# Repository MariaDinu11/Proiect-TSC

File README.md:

# Proiect-TSC

  OpenBook E-Reader
OpenBook este un e-book reader open source si accesibil, proiectat pentru a oferi o experiență bună de citire la un preț competitiv.

## Bill of Materials (BOM)

| Nr. | Componenta | Descriere | Cantitate | Link achizitie | Datasheet |
|-----|------------|-----------|-----------|----------------|-----------|
| 1 | ESP32-C6-WROOM-1-N8 | Modul WiFi/Bluetooth/Zigbee | 1 | [Model](https://www.snapeda.com/parts/ESP32-C6-WROOM-1-N8/Espressif+Systems/view-part/?ref=eda) | [Datasheet](https://www.espressif.com/sites/default/files/documentation/esp32-c6_datasheet_en.pdf) |
| 2 | W25Q512JVEIQ | Memorie Flash NOR 64MB | 1 | [Model](https://www.snapeda.com/parts/W25Q512JVEIQ/Winbond+Electronics/view-part/?ref=eda) | [Datasheet](https://www.winbond.com/resource-files/W25Q512JV%20RevI%2005132020%20Plus.pdf) |
| 3 | DS3231SN# | Modul RTC de inalta precizie | 1 | [Model](https://www.snapeda.com/parts/DS3231SN%23/Analog+Devices/view-part/?ref=eda) | [Datasheet](https://datasheets.maximintegrated.com/en/ds/DS3231.pdf) |
| 4 | MAX17048G+T10 | Controlor pentru monitorizarea bateriei | 1 | [Model](https://www.snapeda.com/parts/MAX17048G+T10/Analog+Devices/view-part/?ref=eda) | [Datasheet](https://datasheets.maximintegrated.com/en/ds/MAX17048-MAX17049.pdf) |
| 5 | BME688 | Senzor integrat de mediu | 1 | [Model](https://www.snapeda.com/parts/BME680/Bosch/view-part/?welcome=home) | [Datasheet](https://www.bosch-sensortec.com/media/boschsensortec/downloads/datasheets/bst-bme688-ds000.pdf) |
| 6 | MCP73831 | Controler de incarcare baterie Li-Po | 1 | [Model](https://www.mouser.co.uk/ProductDetail/Microchip-Technology/MCP73831T-5ACI-OT?qs=hH%252BOa0VZEiAcgAcEkuamXg%3D%3D) | [Datasheet](https://ww1.microchip.com/downloads/en/DeviceDoc/20001984g.pdf) |
| 7 | BD5229G-TR | Detector de tensiune cu timp de intarziere | 1 | [Model](https://componentsearchengine.com/part-view/BD5229G-TR/ROHM%20Semiconductor) | [Datasheet](https://fscdn.rohm.com/en/products/databook/datasheet/ic/power/voltage_detector/bd52xxg-e.pdf) |
| 8 | PFMF.050.1 | Conector USB Type-C | 1 | [Model](https://www.mouser.com/ProductDetail/Amphenol-FCI/PFMF0501?qs=sGAEpiMZZMulM8LYMF8bxyg6IYwX%252B5CgQVcIoLYkYiM%3D) | [Datasheet](https://cdn.amphenol-cs.com/media/wysiwyg/files/drawing/pfmf.pdf) |
| 9 | USBLC6-2SC6Y | Protectie ESD pentru linii USB | 1 | [Model](https://www.snapeda.com/parts/USBLC6-2SC6Y/STMicroelectronics/view-part/?ref=eda) | [Datasheet](https://www.st.com/resource/en/datasheet/usblc6-2.pdf) |
| 10 | 112A-TAAR-R03 | Slot pentru card microSD | 1 | [Model](https://www.mouser.com/ProductDetail/Attend/112A-TAAR-R03?qs=sGAEpiMZZMsg%2By7HCF96QHhTCuZhYGBTHJ9NEpPMzZc%3D) | [Datasheet](https://www.attend.com.tw/sites/default/files/2022-05/112A-TAAR-R03.pdf) |
| 11 | FH34SRJ-24S-0.5SH | Conector pentru ecran e-paper | 1 | [Model](https://www.hirose.com/product/p/CL0684-0832-7-99) | [Datasheet](https://www.hirose.com/product/document?clcode=CL0684-0832-7-99&productname=FH34SRJ-24S-0.5SH(99)&series=FH34&documenttype=Catalog&lang=en&documentid=D49681_en) |
| 12 | DMG2305UX-7 | Tranzistor MOSFET-P 20V/4.2A | 1 | [Model](https://www.diodes.com/part/view/DMG2305UX) | [Datasheet](https://www.diodes.com/assets/Datasheets/DMG2305UX.pdf) |
| 13 | SI1308EDL-T1-GE3 | Tranzistor MOSFET-N 30V/1.5A | 1 | [Model](https://www.snapeda.com/parts/SI1308EDL-T1-GE3/Vishay+Siliconix/view-part/?ref=snap) | [Datasheet](https://www.vishay.com/docs/68732/si1308edl.pdf) |
| 14 | SD0805S020S1R0 | Inductor 1.0µH | 1 | [Model](https://eu.mouser.com/ProductDetail/KYOCERA-AVX/SD0805S020S1R0?qs=jCA%252BPfw4LHbpkAoSnwrdjw%3D%3D) | [Datasheet](http://datasheets.avx.com/schottky.pdf) |
| 15 | MBR0530 | Dioda Schottky 30V/500mA | 3 | [Model](https://www.snapeda.com/parts/MBR0530/Onsemi/view-part/?ref=eda) | [Datasheet](https://www.onsemi.com/pdf/datasheet/mbr0520lt1-d.pdf) |
| 16 | PGB1010603MR | Dioda TVS pentru protectie ESD | 5 | [Model](https://www.snapeda.com/parts/PGB1010603MR/Littelfuse/view-part/?ref=eda) | [Datasheet](https://www.littelfuse.com/media?resourcetype=datasheets&itemid=3d1e98b7-4d37-463c-9380-c56c83b11c3c&filename=littelfuse-pulseguard-pgb1) |
| 17 | CPH3225A | Cristal RTC 32.768kHz | 1 | [Model](https://www.snapeda.com/parts/CPH3225A/Seiko+Instruments/view-part/?ref=eda) | [Datasheet](https://www.sii.co.jp/en/quartz/files/2021/03/CPH3225A_E.pdf) |
| 18 | XC6220A331MR-G | Regulator LDO de tensiune 3.3V | 1 | [Model](https://www.torexsemi.com/products/voltage-regulators/ldo-regulators/xc6220/) | [Datasheet](https://www.torexsemi.com/file/xc6220/XC6220.pdf) |
| 19 | Buton tactil | Butoane pentru Reset, Boot, Change | 3 | [Model](https://industry.panasonic.com/ww/products/industrial-devices/mechanical-components/switches/light-touch-switches/light-touch-switches/evqpuj02k) | [Datasheet](https://industry.panasonic.com/ww/components/devices/mechanical-components/switches/light-touch-switches/products/evqpuj02k) |
| 20 | LEDs SMD 0603 | LED indicator | 1 | [Model](https://www.snapeda.com/parts/KP-1608SURCK/Kingbright/view-part/?ref=search&t=LED%200603) | [Datasheet](https://www.kingbrightusa.com/images/catalog/SPEC/APHHS1608LSURKCGKC.pdf) |
| 21 | QWIIC_RIGHT_ANGLE | Conector I²C Qwiic | 1 | [Model](https://www.sparkfun.com/products/14417) | [Datasheet](https://cdn.sparkfun.com/assets/1/4/d/8/3/Qwiic_Connector_Datasheet.pdf) |
| 22 | Rezistor 10K | SMD 0402 | 12 | [Model](https://componentsearchengine.com/part-view/R0402%201%25%20100%20K%20(RC0402FR-07100KL)/YAGEO) | - |
| 23 | Rezistor 5.1K | SMD 0402 | 2 | [Model](https://www.yageo.com/en/Product/resistors) | - |
| 24 | Rezistor 2K | SMD 0402 | 1 | [Model](https://www.yageo.com/en/Product/resistors) | - |
| 25 | Rezistor 2.2 | SMD 0402 | 1 | [Model](https://www.yageo.com/en/Product/resistors) | - |
| 26 | Rezistor 200 | SMD 0402 | 1 | [Model](https://www.yageo.com/en/Product/resistors) | - |
| 27 | Rezistor 100K | SMD 0402 | 1 | [Model](https://www.yageo.com/en/Product/resistors) | - |
| 28 | Rezistor 15 | SMD 0402 | 1 | [Model](https://www.yageo.com/en/Product/resistors) | - |
| 29 | Rezistor 0.47 | SMD 0402 | 1 | [Model](https://www.yageo.com/en/Product/resistors) | - |
| 30 | Capacitor 100nF | SMD 0402 | 10 | [Model](https://componentsearchengine.com/part-view/CC0402MRX5R5BB106/YAGEO) | - |
| 31 | Capacitor 4.7µF | SMD 0402 | 5 | [Model](https://www.yageo.com/en/Product/mlcc) | - |
| 32 | Capacitor 1µF | SMD 0402 | 10 | [Model](https://www.yageo.com/en/Product/mlcc) | - |
| 33 | Capacitor 1µF/50V | SMD 0402 | 10 | [Model](https://www.yageo.com/en/Product/mlcc) | - |
| 34 | Capacitor 10µF | SMD 0402 | 1 | [Model](https://www.yageo.com/en/Product/mlcc) | - |
| 35 | Capacitor 100µF TANT | SMD CT3528 | 1 | [Model](https://a360.co/4iZy6AA) | - |
| 36 | Test pads | Puncte de testare TP20R | 17 | [Model](https://www.keyelco.com/product.cfm/product_id/1543) | - |
| 37 | SMD Solder Jumper | Jumper SMD | 1 | [Model](https://grabcad.com/library/solder-jumpers-1) | - |

## Functionalitatea Hardware

### Componente Principale

1. **Microcontroller ESP32-C6**
   - Procesor RISC-V cu 8MB Flash
   - WiFi 6 (802.11ax), Bluetooth 5, suport Zigbee si Thread
   - Management optimizat al energiei pentru durata de viata a bateriei

2. **Interfata Display E-Paper**
   - Conectata prin interfata SPI si semnale de control dedicate
   - Circuit special pentru generarea tensiunilor e-paper
   - Consum de energie aproape zero in stare statica

3. **Sistem de Stocare**
   - Flash extern 64MB (W25Q512JVEIQ) pentru fonturi si elemente UI
   - Slot card MicroSD pentru biblioteca extinsa de carti

4. **Management Energie**
   - Circuit incarcare baterie LiPo folosind MCP73831
   - Regulator de tensiune XC6220A331MR-G pentru 3.3V stabil
   - MAX17048G+T10 pentru monitorizare precisa a nivelului bateriei
   - Moduri deep sleep pentru durata extinsa de viata a bateriei

5. **Periferice Auxiliare**
   - Senzor de mediu BME688 (temperatura, umiditate, calitatea aerului)
   - Modul RTC DS3231SN de precizie inalta
   - Conector Qwiic/Stemma QT pentru expansiune
   - Trei butoane tactile pentru navigare

### Tabel detaliat al utilizarii pinilor

| Pin ESP32-C6 | Functie | Conectat la | Justificare |
|--------------|---------|-------------|-------------|
| GPIO 0 | IO/BOOT | Buton BOOT | Pin special cu functie de Boot necesar pentru intrarea in modul de programare |
| GPIO 1 | FLASH_CS | Memorie Flash W25Q512JVEIQ | Chip Select pentru memoria Flash externa, pozitionat logic in apropierea celorlalti pini SPI |
| GPIO 2 | EN | Circuit supervisor BD5229G-TR | Semnal de Enable pentru microcontroller, controlat de supervizorul de tensiune |
| GPIO 3 | SDA | Magistrala I²C | Linie de date pentru interfata I²C care conecteaza senzorul BME688, RTC-ul si monitorul bateriei |
| GPIO 4 | SCL | Magistrala I²C | Linie de clock pentru interfata I²C, cu rezistori pull-up adecvati |
| GPIO 5 | MOSI | Interfata SPI (Flash, E-Paper, SD) | Master Out Slave In pentru comunicatiile SPI, folosit pentru toate dispozitivele SPI |
| GPIO 6 | MISO | Interfata SPI (Flash, SD) | Master In Slave Out pentru comunicatiile SPI, primeste date de la perifericele SPI |
| GPIO 7 | SCK | Interfata SPI (Flash, E-Paper, SD) | Clock pentru interfata SPI, sincronizeaza toate dispozitivele SPI |
| GPIO 8 | USB_D+ | Interfata USB | Linie de date pozitiva USB, conectata la conectorul USB-C prin protectie ESD |
| GPIO 9 | USB_D- | Interfata USB | Linie de date negativa USB, conectata la conectorul USB-C prin protectie ESD |
| GPIO 10 | EPD_CS | E-Paper Display | Chip Select pentru display-ul e-paper, activeaza comunicatia SPI cu acesta |
| GPIO 11 | SS_SD | Card SD | Chip Select pentru cardul SD, permite selectarea independenta a cardului pe magistrala SPI comuna |
| GPIO 12 | EPD_DC | E-Paper Display | Data/Command pentru e-paper, diferentiaza intre comenzi si date pe magistrala SPI |
| GPIO 13 | EPD_RST | E-Paper Display | Reset pentru e-paper, permite reinitializarea hardware a display-ului |
| GPIO 15 | INT_RTC | Modul RTC DS3231SN | Interrupt de la RTC, permite trezirea din sleep la alarme sau evenimente temporizate |
| GPIO 16 | TXD0 | UART Debug/Test | Transmit pentru UART, folosit pentru debug si diagnosticare |
| GPIO 17 | RXD0 | UART Debug/Test | Receive pentru UART, folosit pentru debug si diagnosticare |
| GPIO 18 | EPD_BUSY | E-Paper Display | Semnal Busy de la e-paper, indica cand display-ul proceseaza date |
| GPIO 19 | IO/CHANGE | Buton CHANGE | Intrare pentru butonul de schimbare a optiunilor, cu pull-up intern |
| GPIO 21-23 | Test Pads | Puncte de testare | Pini disponibili pentru testare si diagnosticare |

## Decizii si modificari de design
* Am pozitionat componentele principale conform specificatiilor pentru a asigura compatibilitatea perfecta intre dimensiunile PCB-ului si carcasa. Bateria a fost plasata in spatiul ramas disponibil.
* Am creat planuri de masa atat pe straturile superioare cat si inferioare pentru a imbunatati integritatea semnalului si a reduce zgomotul electromagnetic.
* Rutarea a fost realizata pe ambele straturi, insa am plasat traseele de putere exclusiv pe stratul superior pentru a evita utilizarea via-urilor, conform recomandarilor.
* Am modificat dimensiunile pad-urilor pentru diode la 35 x 190 mil pentru a imbunatati procesul de fabricatie si fiabilitatea contactelor electrice.
* Pentru circuitul MAX17048G+T10, am ajustat latimea pad-urilor pentru a corespunde cu latimea traseului VBAT de 0.3 mm, asigurand o rutare consecventa si un layout mai echilibrat.

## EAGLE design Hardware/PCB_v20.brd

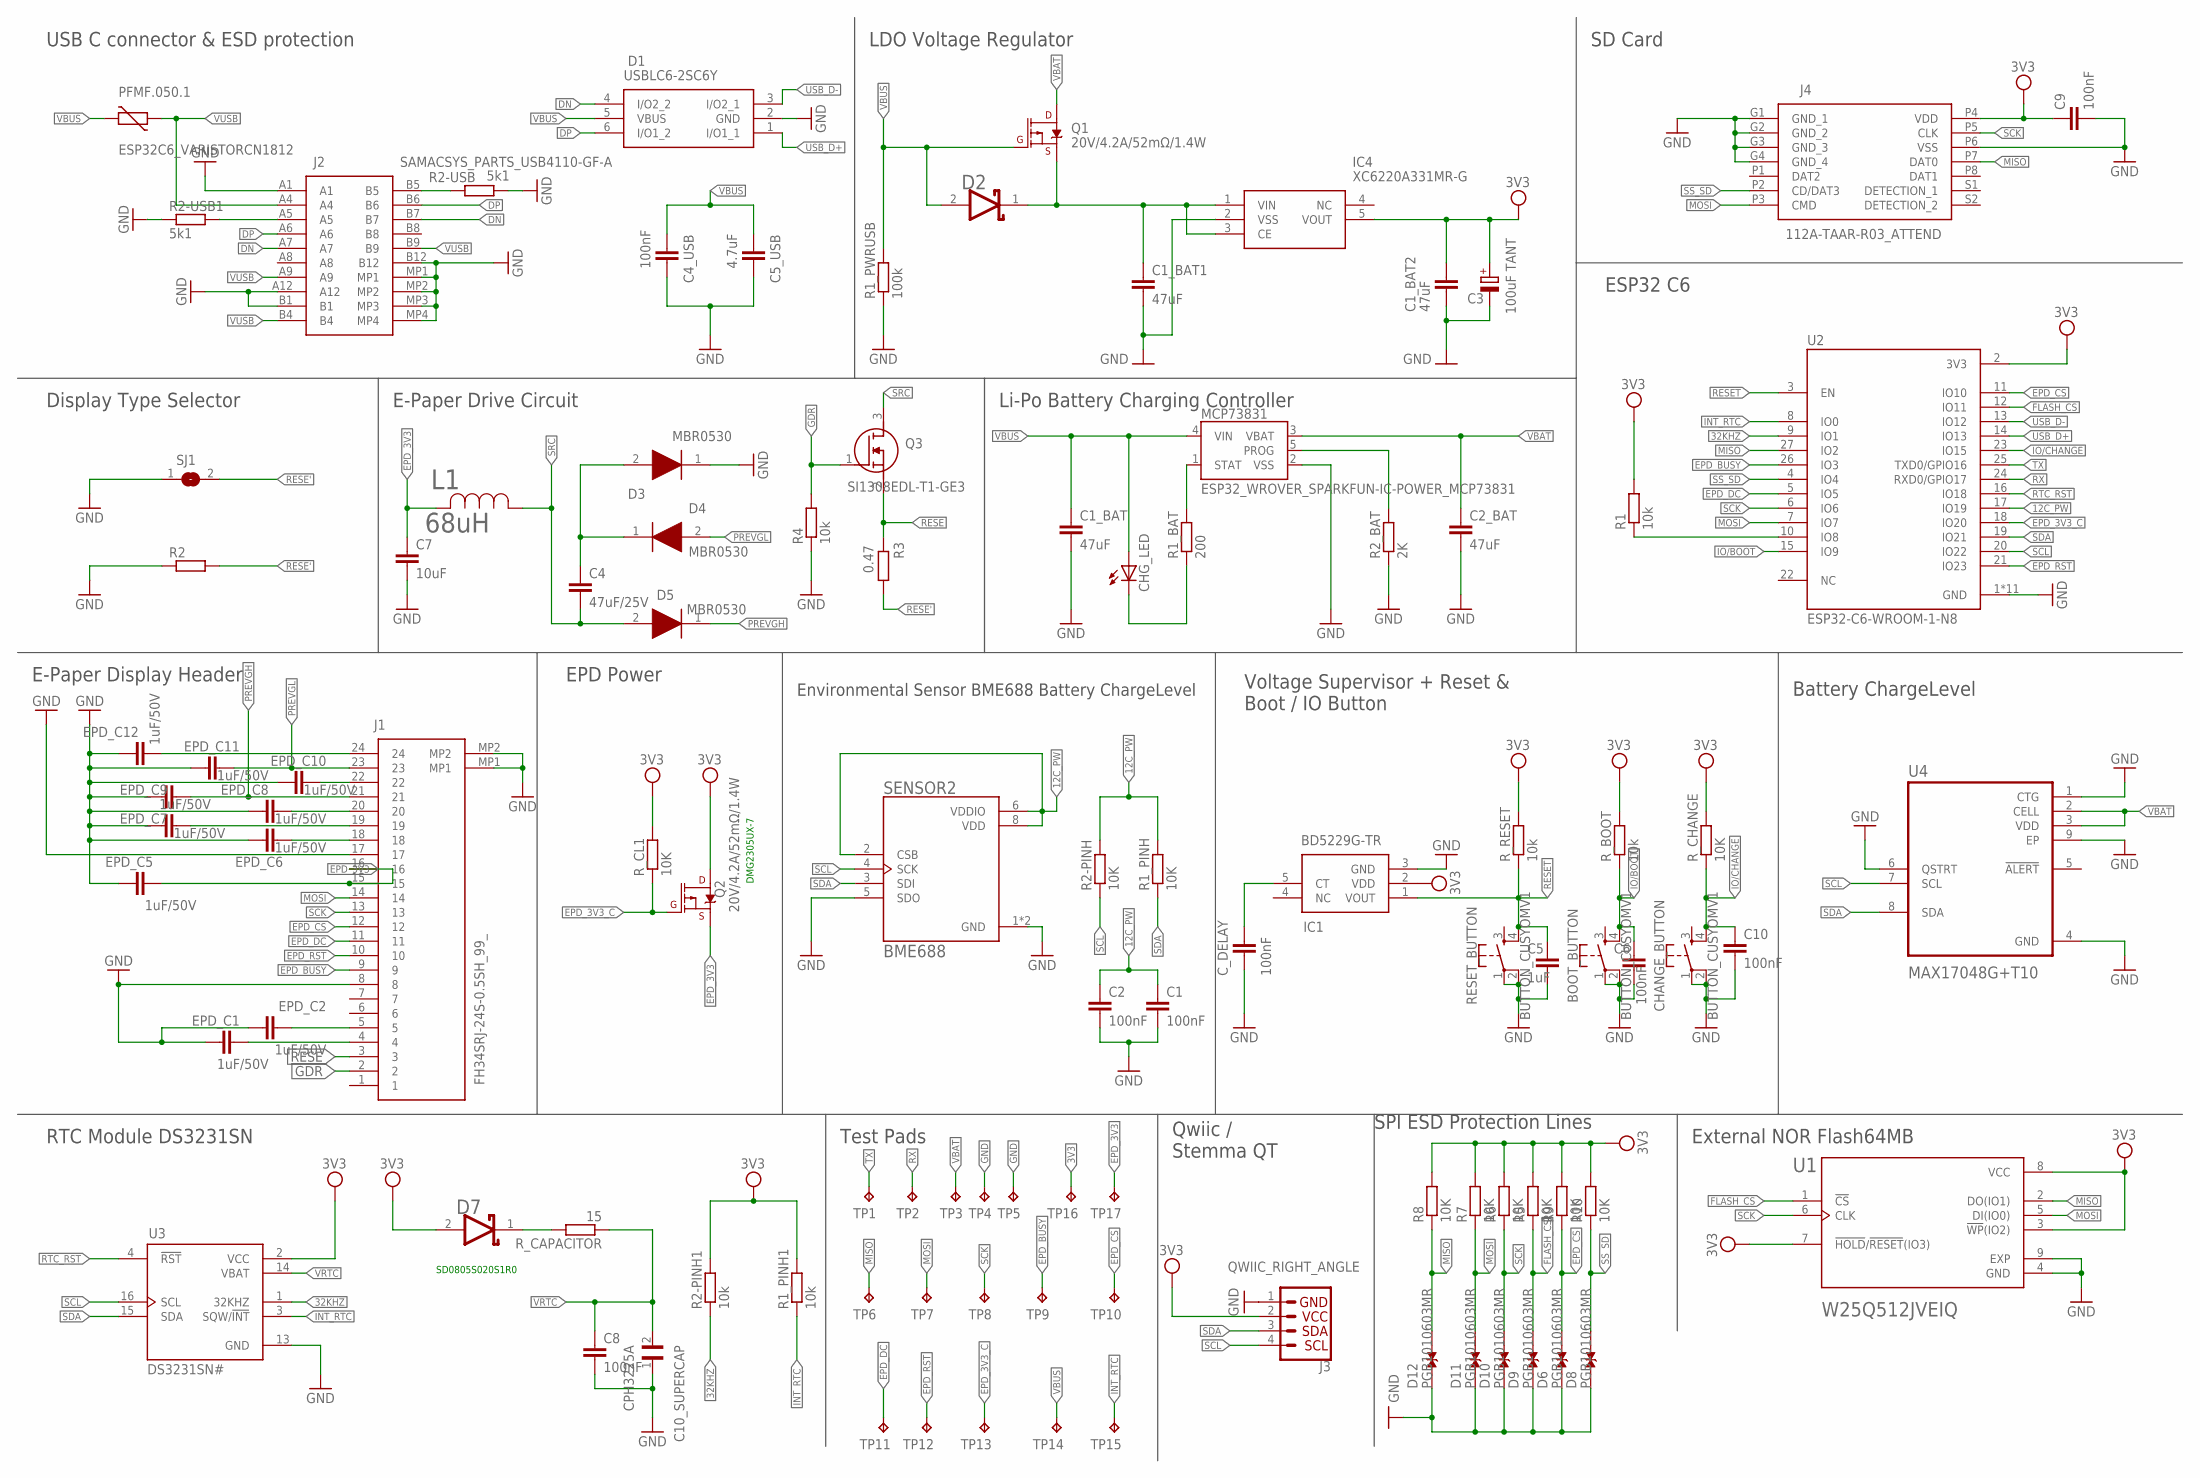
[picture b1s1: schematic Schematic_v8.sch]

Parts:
BOOT_BUTTON: BUTTON_CUSYOMV1; MYBUTTON
C1, C2, C4_USB, C6, C8, C9, C10: 100nF; EAGLE-LTSPICE_C0402
C1_BAT, C1_BAT1, C1_BAT2, C2_BAT: 47uF; EAGLE-LTSPICE_C0402
C3: 100uF TANT; RCL_CT3528
C4: 47uF/25V; EAGLE-LTSPICE_C0402
C5: 1uF; EAGLE-LTSPICE_C0402
C5_USB: 4.7uF; EAGLE-LTSPICE_C0402
C7: 10uF; EAGLE-LTSPICE_C0402
C10_SUPERCAP: CPH3225A; CAPCP3225X100N
CHANGE_BUTTON: BUTTON_CUSYOMV1; MYBUTTON
CHG_LED: ADAFRUIT_LEDCHIP-LED0603; ADAFRUIT_CHIP-LED0603
C_DELAY: 100nF; EAGLE-LTSPICE_C0402
D1: USBLC6-2SC6Y; SOT95P280X145-6N
D2, D7: SD0805S020S1R0; ESP32_WROVER_AVX---SD0805S020S1R0_AVX_SD0805S020S1R0_0
D3, D4, D5: MBR0530; SOD3716X135N
D6, D8, D9, D10, D11, D12: PGB1010603MR; DIOC1608X36N
EPD_C1, EPD_C2, EPD_C5, EPD_C6, EPD_C7, EPD_C8, EPD_C9, EPD_C10, EPD_C11, EPD_C12: 1uF/50V; EAGLE-LTSPICE_C0402
IC1: BD5229G-TR; SOT95P280X125-5N
IC4: XC6220A331MR-G; SOT95P280X120-5N
J1: FH34SRJ-24S-0.5SH_99_; FH34SRJ24S05SH99
J2: SAMACSYS_PARTS_USB4110-GF-A; SAMACSYS_PARTS_USB4110GFA
J3: QWIIC_RIGHT_ANGLE; JST04_1MM_RA
J4: 112A-TAAR-R03_ATTEND; 112ATAARR03ATTEND
L1: 68uH; IND_4828-WE-TPC_WRE
MCP73831: ESP32_WROVER_SPARKFUN-IC-POWER_MCP73831; ESP32_WROVER_SPARKFUN-IC-POWER_SOT23-5
PFMF.050.1: ESP32C6_VARISTORCN1812; ESP32C6_VARISTOR_CT/CN1812
Q1, Q2: 20V/4.2A/52mΩ/1.4W; ESP32_WROVER_SPARKFUN-DISCRETESEMI_SOT23-3
Q3: SI1308EDL-T1-GE3; SOT65P210X110-3N
R1, R1_PINH1, R2-PINH1, R4: 10k; ESP32_WROVER_EAGLE-LTSPICE_R0402
R1_BAT: 200; ESP32_WROVER_EAGLE-LTSPICE_R0402
R1_PINH, R2-PINH, R5, R6, R7, R8, R9, R10: 10K; ESP32_WROVER_EAGLE-LTSPICE_R0402
R1_PWRUSB: 100k; ESP32_WROVER_EAGLE-LTSPICE_R0402
R2: ESP32_WROVER_EAGLE-LTSPICE_RR0402; ESP32_WROVER_EAGLE-LTSPICE_R0402
R2-USB, R2-USB1: 5k1; ESP32_WROVER_EAGLE-LTSPICE_R0402
R2_BAT: 2K; ESP32_WROVER_EAGLE-LTSPICE_R0402
R3: 0.47; ESP32_WROVER_EAGLE-LTSPICE_R0402
RESET_BUTTON: BUTTON_CUSYOMV1; MYBUTTON
R_BOOT: 10k; ESP32_WROVER_EAGLE-LTSPICE_R0402
R_CAPACITOR: 15; ESP32_WROVER_EAGLE-LTSPICE_R0402
R_CHANGE: 10K; ESP32_WROVER_EAGLE-LTSPICE_R0402
R_CL1: 10K; ESP32_WROVER_EAGLE-LTSPICE_R0402
R_RESET: 10k; ESP32_WROVER_EAGLE-LTSPICE_R0402
SENSOR2: BME688; ESP32_WROVER_BME680_PSON80P300X300X100-8N
SJ1: SJ
TP1, TP2, TP3, TP4, TP5, TP6, TP7, TP8, TP9, TP10, TP11, TP12, TP13, TP14, TP15, TP16, TP17: TPTP20R; TP20R
U1: W25Q512JVEIQ; SON127P600X800X80-9N
U2: ESP32-C6-WROOM-1-N8; XCVR_ESP32-C6-WROOM-1-N8
U3: DS3231SN#; SOIC127P1032X265-16N
U4: MAX17048G+T10; SON50P200X200X80-9N

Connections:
3V3: C1_BAT2.1, C3.+, C9.1, D7.2 (ANODE), IC1.2 (VDD), IC4.5 (VOUT), J3.2, J4.P4 (VDD), Q2.3 (D), R1.2, R1_PINH1.2, R2-PINH1.2, R5.2, R6.2, R7.2, R8.2, R9.2, R10.2, R_BOOT.2, R_CHANGE.2, R_CL1.2, R_RESET.2, TP16.TP, U1.3 (!WP!(IO2)), U1.7 (!HOLD!/!RESET!(IO3)), U1.8 (VCC), U2.2 (3V3), U3.2 (VCC)
12C_PW: C1.1, C2.1, R1_PINH.2, R2-PINH.2, SENSOR2.2 (CSB), SENSOR2.6 (VDDIO), SENSOR2.8 (VDD), U2.16 (IO18)
32KHZ: R2-PINH1.1, U2.9 (IO1), U3.1 (32KHZ)
DN: D1.4 (I/O2_2), J2.A7, J2.B7
DP: D1.6 (I/O1_2), J2.A6, J2.B6
EPD_3V3: C7.1, EPD_C5.2, J1.15, J1.16, L1.2, Q2.2 (S), TP17.TP
EPD_3V3_C: Q2.1 (G), R_CL1.1, TP13.TP, U2.18 (IO20)
EPD_BUSY: J1.9, TP9.TP, U2.26 (IO3)
EPD_CS: D6.2, J1.12, R9.1, TP10.TP, U2.11 (IO10)
EPD_DC: J1.11, TP11.TP, U2.5 (IO5)
EPD_RST: J1.10, TP12.TP, U2.21 (IO23)
FLASH_CS: D9.2, R5.1, U1.1 (!CS), U2.12 (IO11)
GDR: J1.2, Q3.1 (G), R4.2
GND: BOOT_BUTTON.1, BOOT_BUTTON.2, C1.2, C1_BAT.2, C1_BAT1.2, C1_BAT2.2, C2.2, C2_BAT.2, C3.-, C4_USB.2, C5.2, C5_USB.2, C6.2, C7.2, C8.2, C9.2, C10.2, C10_SUPERCAP.1, CHANGE_BUTTON.1, CHANGE_BUTTON.2, C_DELAY.2, D1.2 (GND), D3.1 (K), D6.1, D8.1, D9.1, D10.1, D11.1, D12.1, EPD_C1.1, EPD_C2.1, EPD_C5.1, EPD_C6.1, EPD_C7.1, EPD_C8.1, EPD_C9.1, EPD_C10.1, EPD_C11.1, EPD_C12.1, IC1.3 (GND), IC4.2 (VSS), J1.8, J1.17, J1.MP1, J1.MP2, J2.A1, J2.A12, J2.B1, J2.B12, J2.MP1, J2.MP2, J2.MP3, J2.MP4, J3.1, J4.G1 (GND_1), J4.G2 (GND_2), J4.G3 (GND_3), J4.G4 (GND_4), J4.P6 (VSS), MCP73831.2 (VSS), R1_PWRUSB.1, R2.1, R2-USB.2, R2-USB1.1, R2_BAT.1, R4.1, RESET_BUTTON.1, RESET_BUTTON.2, SENSOR2.1 (GND), SENSOR2.5 (SDO), SENSOR2.7 (GND), SJ1.1, TP4.TP, TP5.TP, U1.4 (GND), U1.9 (EXP), U2.1 (GND), U2.28 (GND), U2.29_1 (GND), U2.29_2 (GND), U2.29_3 (GND), U2.29_4 (GND), U2.29_5 (GND), U2.29_6 (GND), U2.29_7 (GND), U2.29_8 (GND), U2.29_9 (GND), U3.13 (GND), U4.1 (CTG), U4.4 (GND), U4.6 (QSTRT), U4.9 (EP)
INT_RTC: R1_PINH1.1, TP15.TP, U2.8 (IO0), U3.3 (SQW/!INT)
IO/BOOT: BOOT_BUTTON.4, C6.1, R_BOOT.1, U2.15 (IO9)
IO/CHANGE: C10.1, CHANGE_BUTTON.4, R_CHANGE.1, U2.23 (IO15)
MISO: D12.2, J4.P7 (DAT0), R8.1, TP6.TP, U1.2 (DO(IO1)), U2.27 (IO2)
MOSI: D11.2, J1.14, J4.P3 (CMD), R7.1, TP7.TP, U1.5 (DI(IO0)), U2.7 (IO7)
unnamed: J2.A5, R2-USB1.2
unnamed: J2.B5, R2-USB.1
unnamed: C1_BAT1.1, D2.1 (CATHODE), IC4.1 (VIN), IC4.3 (CE), Q1.2 (S)
unnamed: C4.1, D3.2 (A), D4.1 (K)
unnamed: C_DELAY.1, IC1.5 (CT)
unnamed: CHG_LED.C, R1_BAT.1
unnamed: MCP73831.1 (STAT), R1_BAT.2
unnamed: MCP73831.5 (PROG), R2_BAT.2
unnamed: EPD_C12.2, J1.24
unnamed: EPD_C10.2, J1.22
unnamed: EPD_C7.2, J1.19
unnamed: EPD_C8.2, J1.20
unnamed: D7.1 (CATHODE), R_CAPACITOR.2
unnamed: EPD_C6.2, J1.18
unnamed: R1.1, U2.10 (IO8)
unnamed: EPD_C2.2, J1.5
unnamed: EPD_C1.2, J1.4
PREVGH: D5.1 (K), EPD_C9.2, J1.21
PREVGL: D4.2 (A), EPD_C11.2, J1.23
RESE: J1.3, Q3.2 (S), R3.2
RESE': R2.2, R3.1, SJ1.2
RESET: C5.1, IC1.1 (VOUT), RESET_BUTTON.4, R_RESET.1, U2.3 (EN)
RTC_RST: U2.17 (IO19), U3.4 (!RST)
RX: TP2.TP, U2.24 (RXD0/GPIO17)
SCK: D10.2, J1.13, J4.P5 (CLK), R6.1, TP8.TP, U1.6 (CLK), U2.6 (IO6)
SCL: J3.4, R2-PINH.1, SENSOR2.4 (SCK), U2.20 (IO22), U3.16 (SCL), U4.7 (SCL)
SDA: J3.3, R1_PINH.1, SENSOR2.3 (SDI), U2.19 (IO21), U3.15 (SDA), U4.8 (SDA)
SRC: C4.2, D5.2 (A), L1.1, Q3.3 (D)
SS_SD: D8.2, J4.P2 (CD/DAT3), R10.1, U2.4 (IO4)
TX: TP1.TP, U2.25 (TXD0/GPIO16)
USB_D+: D1.1 (I/O1_1), U2.14 (IO13)
USB_D-: D1.3 (I/O2_1), U2.13 (IO12)
VBAT: C2_BAT.1, MCP73831.3 (VBAT), Q1.3 (D), TP3.TP, U4.2 (CELL), U4.3 (VDD)
VBUS: C1_BAT.1, C4_USB.1, C5_USB.1, CHG_LED.A, D1.5 (VBUS), D2.2 (ANODE), MCP73831.4 (VIN), PFMF.050.1.2, Q1.1 (G), R1_PWRUSB.2, TP14.TP
VRTC: C8.1, C10_SUPERCAP.2, R_CAPACITOR.1, U3.14 (VBAT)
VUSB: J2.A4, J2.A9, J2.B4, J2.B9, PFMF.050.1.1

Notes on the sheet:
DMG2305UX-7
SD0805S020S1R0
USB C connector & ESD protection
LDO Voltage Regulator
SD Card
Display Type Selector
E-Paper Drive Circuit
Li-Po Battery Charging Controller
ESP32 C6
E-Paper Display Header
EPD Power
Environmental Sensor BME688 Battery ChargeLevel
Voltage Supervisor + Reset & Boot / IO Button
Battery ChargeLevel
External NOR Flash64MB
SPI ESD Protection Lines
Qwiic / Stemma QT
Test Pads
RTC Module DS3231SN

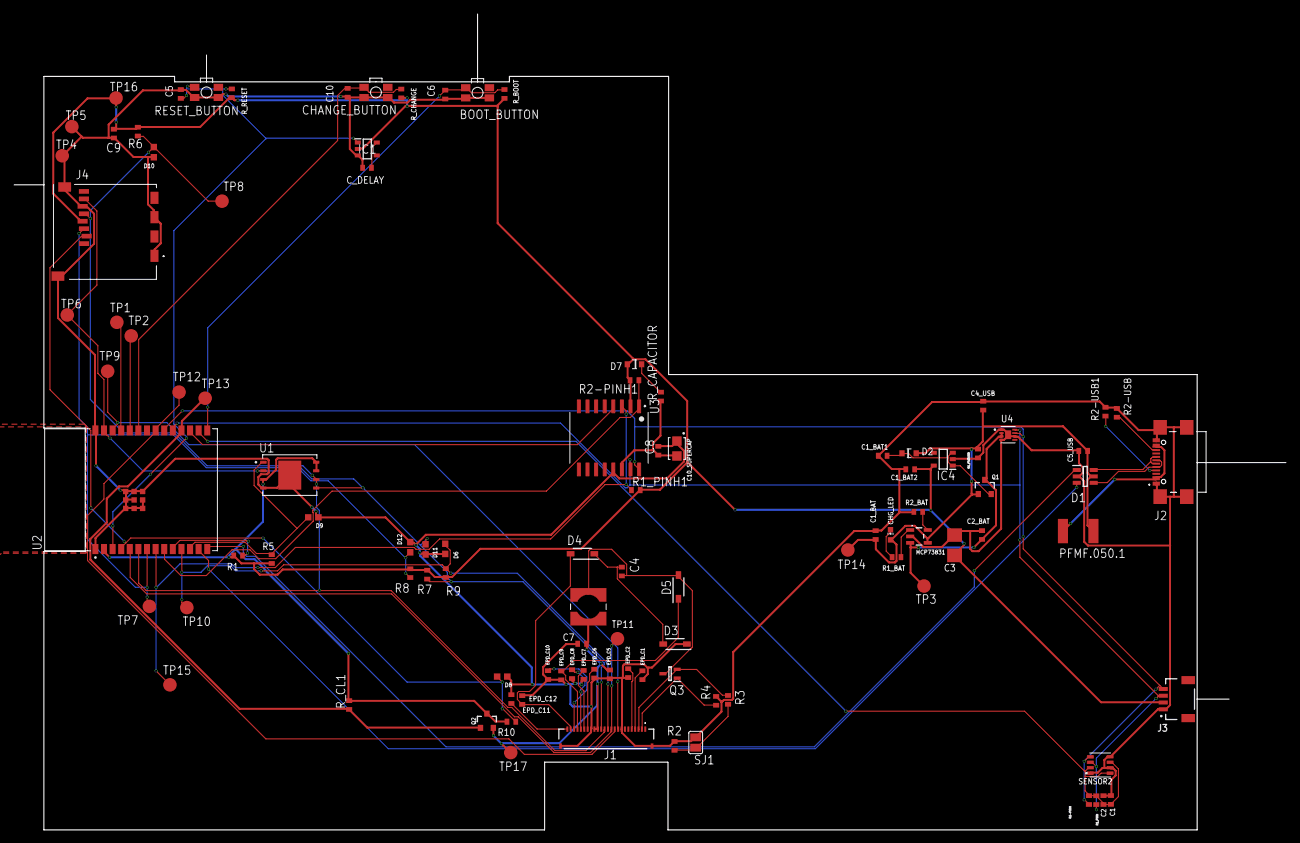
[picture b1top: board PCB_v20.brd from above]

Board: 2 copper layers, 170.2 x 111.2 mm, 103 parts (0 on the bottom side), 55 nets.

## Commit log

2025-04-06 Create a
2025-04-06 Create LICENSE
2025-04-15 Add files via upload
    actualizare

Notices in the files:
parts and their libraries:
COPYRIGHT: Copyright (C) 2024 Ultra Librarian. All rights reserved.
